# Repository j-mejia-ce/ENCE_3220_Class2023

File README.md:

# ENCE_3220_Class2023
Embedded Systems - Spring 2023

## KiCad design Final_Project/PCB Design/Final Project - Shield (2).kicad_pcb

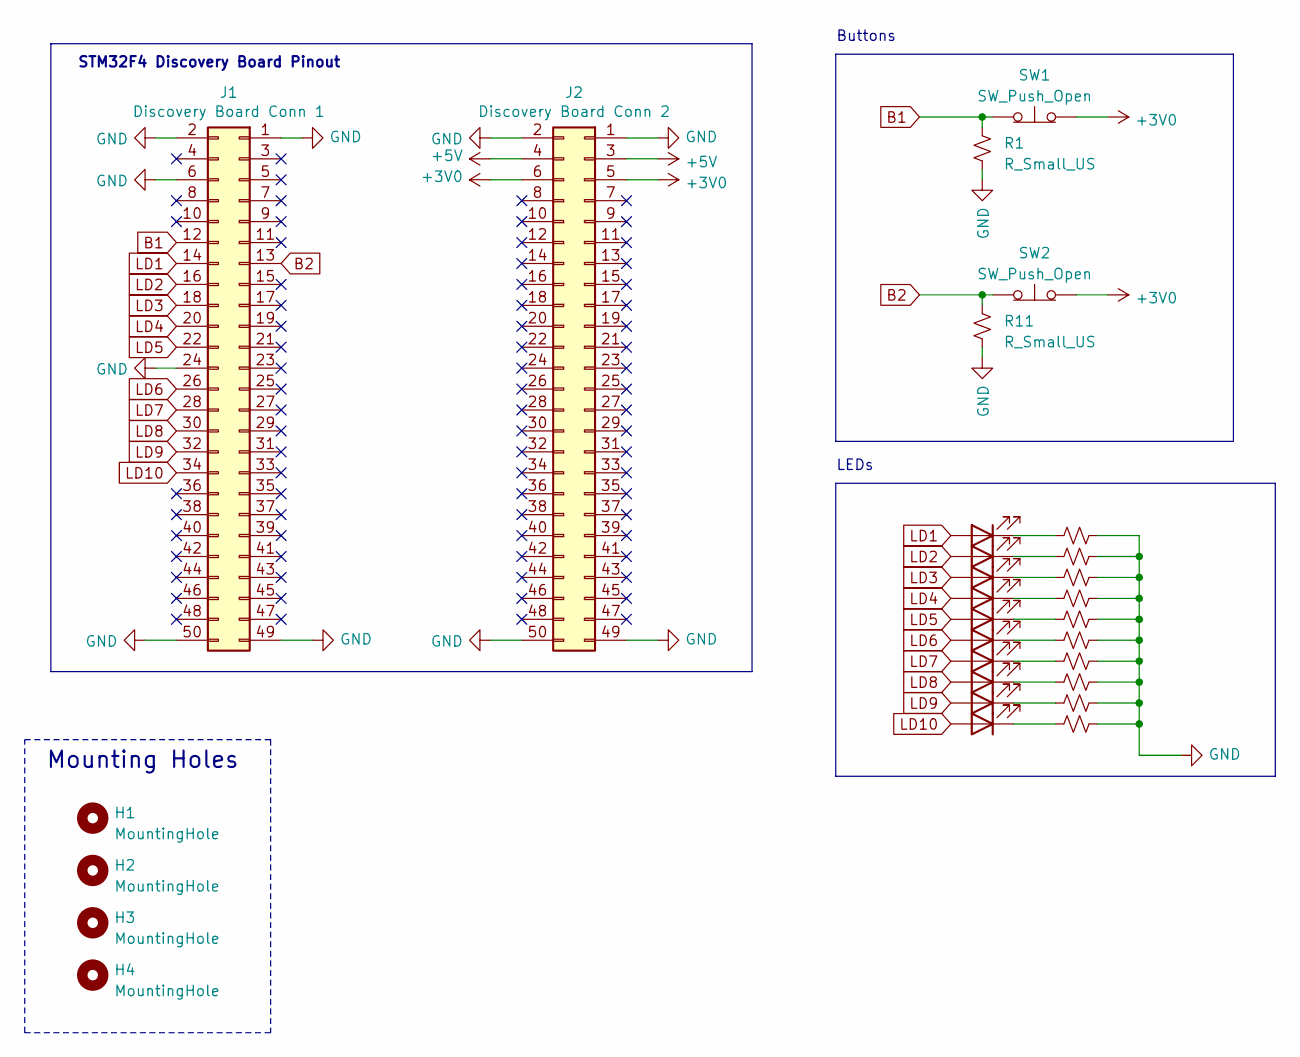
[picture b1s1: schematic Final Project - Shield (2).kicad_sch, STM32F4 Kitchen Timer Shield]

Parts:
D1, D2, D3, D4, D5, D6, D7, D8, D9, D10: LED; LED-L1T2_LUMILEDS
H1, H2, H3, H4: MountingHole; MountingHole_3.2mm_M3_Pad
J1: Discovery Board Conn 1; PinSocket_2x25_P2.54mm_Vertical
J2: Discovery Board Conn 2; PinSocket_2x25_P2.54mm_Vertical
R1, R2, R3, R4, R5, R6, R7, R8, R9, R10, R11, R12: R_Small_US; R_0201_0603Metric
SW1, SW2: SW_Push_Open; SW_SPST_PTS810

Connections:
+3V0: J2.5, J2.6, SW1.2 (B), SW2.2 (B)
+5V: J2.3, J2.4
B1: J1.12, R1.2, SW1.1 (A)
B2: J1.13, R11.2, SW2.1 (A)
GND: J1.1, J1.2, J1.6, J1.24, J1.49, J1.50, J2.1, J2.2, J2.49, J2.50, R1.1, R2.1, R3.1, R4.1, R5.1, R6.1, R7.1, R8.1, R9.1, R10.1, R11.1, R12.1
LD1: D1.2 (A), J1.14
LD2: D2.2 (A), J1.16
LD3: D3.2 (A), J1.18
LD4: D4.2 (A), J1.20
LD5: D5.2 (A), J1.22
LD6: D6.2 (A), J1.26
LD7: D7.2 (A), J1.28
LD8: D8.2 (A), J1.30
LD9: D9.2 (A), J1.32
LD10: D10.2 (A), J1.34
unnamed: D1.1 (K), R12.2
unnamed: D2.1 (K), R2.2
unnamed: D3.1 (K), R3.2
unnamed: D4.1 (K), R4.2
unnamed: D5.1 (K), R5.2
unnamed: D6.1 (K), R6.2
unnamed: D7.1 (K), R7.2
unnamed: D8.1 (K), R8.2
unnamed: D9.1 (K), R9.2
unnamed: D10.1 (K), R10.2

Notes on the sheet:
LEDs
Mounting Holes
STM32F4 Discovery Board Pinout
Buttons

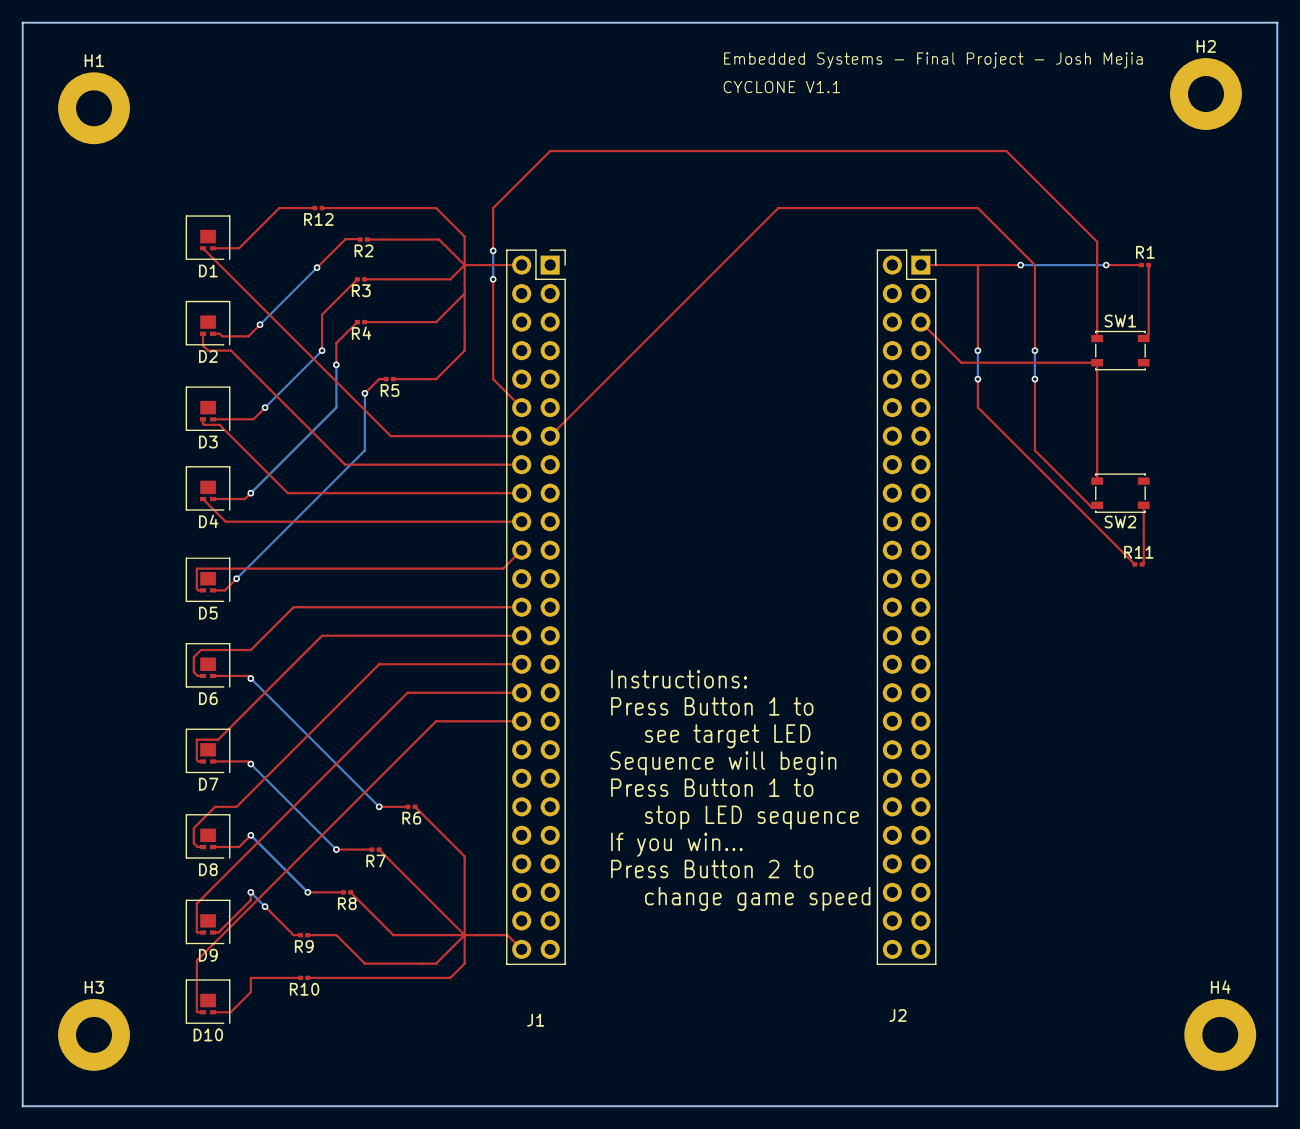
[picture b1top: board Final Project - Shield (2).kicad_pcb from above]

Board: 2 copper layers, 111.8 x 96.5 mm, 30 parts (0 on the bottom side), 25 nets.

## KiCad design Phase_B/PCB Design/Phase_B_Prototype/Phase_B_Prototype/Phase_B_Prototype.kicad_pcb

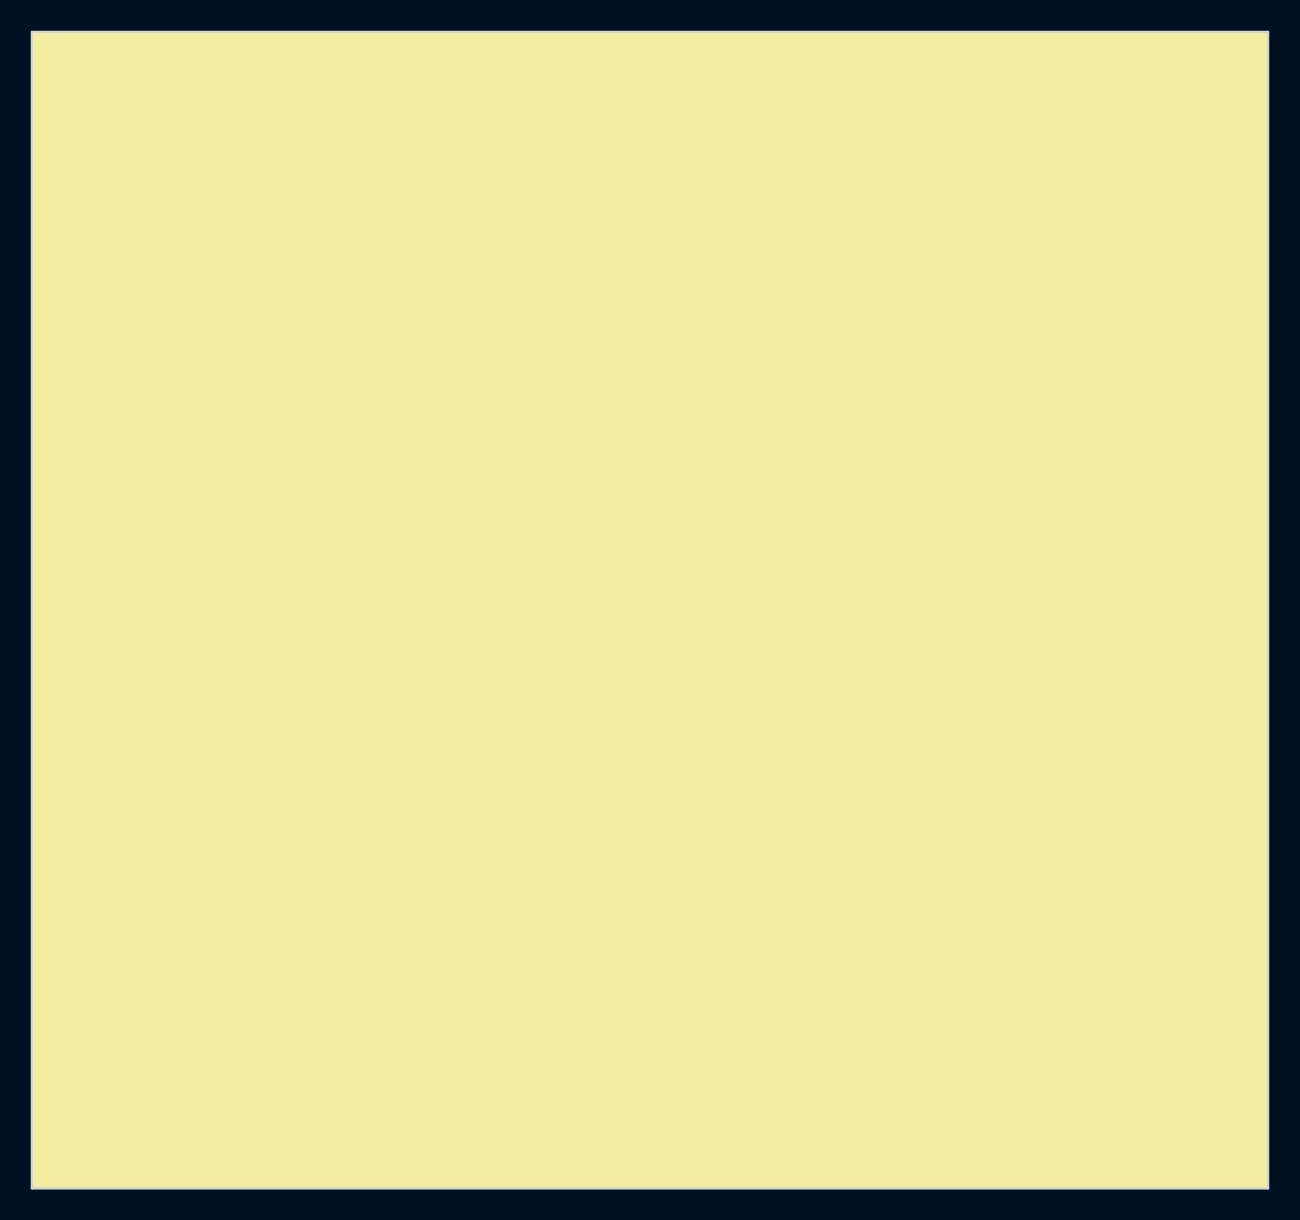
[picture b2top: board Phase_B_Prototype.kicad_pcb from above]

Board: 2 copper layers, 78.7 x 73.7 mm, 49 parts (0 on the bottom side), 53 nets.

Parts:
C1: 0.1u; C_0603_1608Metric
C2, C3: 22p; C_0603_1608Metric
C4, C5, C6, C7, C10, C11, C12: 0.1uF; C_0603_1608Metric
C8: 10uF; C_0805_2012Metric
C9, C13: 1uF; C_0603_1608Metric
C14: 2.2uF; C_0603_1608Metric
C15: 10nF; C_0603_1608Metric
D1, D2, D3: LED; LED_0805_2012Metric
F1: PTCSMD; Fuse_1812_4532Metric
J1: AVR-ISP-6; PinSocket_2x03_P2.54mm_Vertical
J2: USB_B_Mini; USB_Mini-B_Lumberg_2486_01_Horizontal
J3: ESP_Conn; PinSocket_2x04_P2.54mm_Vertical
LS1: Speaker; Buzzer_12x9.5RM7.6
R1, R2: 10k; R_0805_2012Metric
R3, R4: 330; R_0805_2012Metric
R5, R6, R7, R8, R9, R10, R11, R12: 100; R_0805_2012Metric
R13, R17: 10k; R_0603_1608Metric
R14, R15: 22; R_0603_1608Metric
R16: 1k; R_0603_1608Metric
S1, S2: PTS125SM43SMTR21M_LFS; PTS125_SMD_Button
S3: PTS526_SM08_SMTR2_LFS; PTS526_SMD_Button
U1: CA56-12EWA
U2: 74HC595; TSSOP-16_4.4x5mm_P0.65mm
U3: ATmega32U4-A; TQFP-44_10x10mm_P0.8mm
U4: USBLC6-2SC6; SOT-23-6
U5: LP2985-3.3; SOT-23-5
Y1: 16MHz; Crystal_SMD_Abracon_ABM8G-4Pin_3.2x2.5mm

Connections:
+3.3V: C14.1, J3.4, J3.6, J3.8, R17.1, U5.5 (VOUT)
+5V: C1.1, C4.1, C5.1, C6.1, C7.1, C8.1, C10.1, C11.1, C13.1, F1.2, J1.2 (VCC), R13.1, R16.1, S1.C1 (COM_1), S2.C1 (COM_1), U2.10 (~SRCLR), U2.16 (VCC), U3.2 (UVCC), U3.7 (VBUS), U3.14 (VCC), U3.24 (AVCC), U3.34 (VCC), U3.44 (AVCC), U4.5 (VBUS), U5.1 (VIN), U5.3 (ON/~OFF)
/AREF: C12.1, U3.42 (AREF)
/UCAP: C9.1, U3.6 (UCAP)
Button_1: R1.1, S1.B1 (NO_2), U3.19 (PD1)
Button_2: R2.1, S2.B1 (NO_2), U3.18 (PD0)
Buzzer: LS1.1, U3.27 (PD7)
DS: U2.14 (SER), U3.29 (PB5)
Dig1: U1.12 (CA1), U3.32 (PC7)
Dig2: U1.9 (CA2), U3.26 (PD6)
Dig3: U1.8 (CA3), U3.12 (PB7)
Dig4: U1.6 (CA4), U3.30 (PB6)
GND: C1.2, C2.1, C3.2, C4.2, C5.2, C6.2, C7.2, C8.2, C9.2, C10.2, C11.2, C12.2, C13.2, C14.2, C15.2, D1.1 (K), D2.1 (K), D3.1 (K), J1.6 (GND), J2.5 (GND), J3.1, LS1.2, R1.2, R2.2, S3.1, U2.8 (GND), U2.13 (~OE), U3.5 (UGND), U3.15 (GND), U3.23 (GND), U3.33 (~HWB/PE2), U3.35 (GND), U3.43 (GND), U4.2 (GND), U5.2 (GND), Y1.2, Y1.4
GREEN_LED: R4.1, U3.25 (PD4)
MISO: J1.1 (MISO), U3.11 (PB3)
MOSI: J1.4 (MOSI), U3.10 (PB2)
unnamed: D1.2 (A), R3.2
unnamed: D2.2 (A), R4.2
unnamed: D3.2 (A), R16.2
unnamed: J2.3 (D+), R14.1
unnamed: J2.2 (D-), R15.1
unnamed: F1.1, J2.1 (VBUS)
unnamed: J3.5, R17.2
unnamed: R12.2, U1.3 (DPX)
unnamed: R5.2, U1.11 (a)
unnamed: R6.2, U1.7 (b)
unnamed: R7.2, U1.4 (c)
unnamed: R8.2, U1.2 (d)
unnamed: R9.2, U1.1 (e)
unnamed: R10.2, U1.10 (f)
unnamed: R11.2, U1.5 (g)
unnamed: C15.1, U5.4 (BP)
RED_LED: R3.1, U3.31 (PC6)
RST: J1.5 (~RST), R13.2, S3.3, U3.13 (~RESET)
RX: J3.7, U3.21 (PD3)
SCK: J1.3 (SCK), U3.9 (PB1)
SH_CP: U2.11 (SRCLK), U3.1 (PE6)
ST_CP: U2.12 (RCLK), U3.28 (PB4)
TX: J3.2, U3.20 (PD2)
USB_CONN_D+: R14.2, U4.3 (I/O2)
USB_CONN_D-: R15.2, U4.1 (I/O1)
USB_D+: U3.4 (D+), U4.4 (I/O2)
USB_D-: U3.3 (D-), U4.6 (I/O1)
XTAL1: C2.2, U3.17 (XTAL1), Y1.1
XTAL2: C3.1, U3.16 (XTAL2), Y1.3
a: R5.1, U2.15 (QA)
b: R6.1, U2.1 (QB)
c: R7.1, U2.2 (QC)
d: R8.1, U2.3 (QD)
dp: R12.1, U2.7 (QH)
e: R9.1, U2.4 (QE)
f: R10.1, U2.5 (QF)
g: R11.1, U2.6 (QG)

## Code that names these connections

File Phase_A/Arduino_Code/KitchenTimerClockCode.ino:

// This code designed by Bryce Swearingen and Josh Mejia
// It is not fully functional

#define BUTTON_1  2
#define BUTTON_2  3
#define GREEN_LED 4
#define RED_LED   5
//#define BUZZER    6

#define DATA      9
#define LATCH     8
#define CLOCK     7

#define DIGIT_4   10
#define DIGIT_3   11
#define DIGIT_2   12
#define DIGIT_1   13
 
 // redid char table with binary values because we couldn't
 // figure out which hex values were impacting our  display
unsigned char table[]=
{ 0b00111111, // 0
  0b00000110, // 1
  0b01011011, // 2
  0b01001111, // 3
  0b01100110, // 4
  0b01101101, // 5
  0b01111101, // 6
  0b00000111, // 7
  0b01111111, // 8
  0b01101111  // 9
  };

// values for counter and initilization
unsigned char count = 30;
unsigned char initialValue = 30;
unsigned int buttonState = 0;  // variable for reading the pushbutton status
int countdown = 10;

volatile unsigned char isr_1_flag = 0;
volatile unsigned char isr_2_flag = 0;
volatile unsigned char isr_3_flag = 0;

void setup() {
 // LEDs Pins
  pinMode(RED_LED, OUTPUT);
  pinMode(GREEN_LED, OUTPUT);

  // Button Pins
  pinMode(BUTTON_1, INPUT_PULLUP);
  attachInterrupt(digitalPinToInterrupt(BUTTON_1), Button_1_ISR, CHANGE);
  pinMode(BUTTON_2, INPUT_PULLUP);
  attachInterrupt(digitalPinToInterrupt(BUTTON_2), Button_2_ISR, CHANGE);

  // 7-Seg Display
  pinMode(DIGIT_1, OUTPUT);
  pinMode(DIGIT_2, OUTPUT);
  pinMode(DIGIT_3, OUTPUT);
  pinMode(DIGIT_4, OUTPUT);

  // Shift Register Pins
  pinMode(LATCH, OUTPUT);
  pinMode(CLOCK, OUTPUT);
  pinMode(DATA, OUTPUT);

  //disp_on();

  // initialize timer1 
  // single interrupt setup - later versions may include another
  noInterrupts();           // disable all interrupts
  TCCR1A = 0;
  TCCR1B = 0;
  TCNT1  = 0;
  OCR1A = 62500 / 1000;            // compare match register 16MHz/256
  TCCR1B |= (1 << WGM12);   // CTC mode
  TCCR1B |= (1 << CS12);    // 256 prescaler 
  TIMSK1 |= (1 << OCIE1A);  // enable timer compare interrupt
  interrupts();             // enable all interrupts
}

// function for displaying each of the four 7-segments
// each value is based on the countdown and the initial time
void Display_Numbers()
{
  disp_on1();
  digitalWrite(LATCH, LOW);
  shiftOut(DATA, CLOCK, MSBFIRST, table[0]);
  digitalWrite(LATCH, HIGH);
  delay(250);
  disp_on2();
  digitalWrite(LATCH, LOW);
  shiftOut(DATA, CLOCK, MSBFIRST, table[0]);
  digitalWrite(LATCH, HIGH);
  delay(250);
  disp_on3();
  digitalWrite(LATCH, LOW);
  shiftOut(DATA, CLOCK, MSBFIRST, table[countdown / 10]);
  digitalWrite(LATCH, HIGH);
  delay(250);
  disp_on4();
  digitalWrite(LATCH, LOW);
  shiftOut(DATA, CLOCK, MSBFIRST, table[countdown % 10]);
  digitalWrite(LATCH, HIGH);
  delay(250);
  countdown = countdown-0.000001;
  
}

// four different display functions to activate each 7-segment seperately
void disp_on1()
{
   digitalWrite(DIGIT_1, LOW);
   digitalWrite(DIGIT_2, HIGH);
   digitalWrite(DIGIT_3, HIGH);
   digitalWrite(DIGIT_4, HIGH);
}
void disp_on2()
{
   digitalWrite(DIGIT_1, HIGH);
   digitalWrite(DIGIT_2, LOW);
   digitalWrite(DIGIT_3, HIGH);
   digitalWrite(DIGIT_4, HIGH);
}
void disp_on3()
{
   digitalWrite(DIGIT_1, HIGH);
   digitalWrite(DIGIT_2, HIGH);
   digitalWrite(DIGIT_3, LOW);
   digitalWrite(DIGIT_4, HIGH);
}
void disp_on4()
{
   digitalWrite(DIGIT_1, HIGH);
   digitalWrite(DIGIT_2, HIGH);
   digitalWrite(DIGIT_3, HIGH);
   digitalWrite(DIGIT_4, LOW);
}

void Button_1_ISR()
{
  unsigned int buttonState = 0;  // variable for reading the pushbutton status
    
  buttonState = digitalRead(BUTTON_1);
  digitalWrite(RED_LED, buttonState);

  count++;
  Display_Numbers();
}

void Button_2_ISR()
{ 
  unsigned int buttonState = 0;  // variable for reading the pushbutton status
   
  buttonState = digitalRead(BUTTON_2);
  digitalWrite(GREEN_LED, buttonState);
}

ISR(TIMER1_COMPA_vect) // timer compare interrupt service routine
{
  // Set ISR Flag
  isr_3_flag = 1;
}

void loop() {
   Display_Numbers();
  // Attend Button 1
  if(isr_1_flag == 1)
  {
    // Reset ISR Flag
    isr_1_flag = 0;

    // Code
    count++;
    if (count > initialValue){
      count = 0;
    }
    buttonState = digitalRead(BUTTON_1);
    digitalWrite(RED_LED, buttonState);
  }

  // Attend Button 2
  if(isr_2_flag == 1)
  {
    // Reset ISR Flag
    isr_2_flag = 0;
    
    // Code
    buttonState = digitalRead(BUTTON_2);
    digitalWrite(GREEN_LED, buttonState);
  }

  // Attend 7-Seg Display
  if(isr_3_flag == 1)
  {
    // Reset ISR Flag
    isr_3_flag = 0;

    // Code
    //count--;
  }
}

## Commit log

2023-04-07 Phase A - Beta Release
2023-04-21 Phase B
2023-05-04 Create readme
    Phase B
2023-05-04 Add files via upload
    Phase B
2023-05-04 Phase B
    Enclosure Top
2023-05-04 Phase B
    BOM html
2023-05-04 Phase B
    Kitchen Timer Code
2023-05-04 Create Kitchen Timer Code
2023-05-04 Create read me
2023-05-04 Phase B
    Kitchen Timer Clock Code
2023-05-11 Phase C
2023-05-29 Final Project
2023-06-01 Add files via upload
    Final Project
2023-06-08 Phase B
    JM Design
